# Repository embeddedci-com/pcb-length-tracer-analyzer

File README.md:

# pcb-trace-length-analyzer

A PCB trace length analyzer for KiCad boards. Reads a `.kicad_pcb`, finds the
interfaces on it -- DDR, Ethernet, USB, PCIe, MIPI, SD and any differential
pair -- measures how far each net is from the length it should be, and says what
to do about each one: match it where it is, open some room beside it, or route
it to a given length instead.

It can also fold the meanders in for you. That half is opt-in and experimental;
the analysis is the product.

DDR is the one it plans and tunes in full, because it is the hardest case: byte
lanes matched to their own strobe, address and command matched to the clock per
leg of the fly-by chain. The rest are recognised from the net names, measured,
and reported for you to confirm or correct.

It does not route. Nothing here creates a connection, moves a via, changes a
layer or rips anything up: a straight stretch of an existing track is replaced
by a longer path between the same two points, and everything else is left
exactly as it was.

**Reading a board is the solid half; writing to one is experimental.** The
report, the measurements and the triage are what this tool is for and are
checked against KiCad and against golden lengths. The changes it writes are
checked against KiCad's own DRC on the boards here and behave -- but no board
tuned by this has come back from a fab and been measured. Run DRC on the
result, look at the copper, and treat what comes out as a draft. Your own file
is never written to; the result is always a new one.

## Layout

```
cmd/pcb-trace-length-analyzer/        the command line tool
cmd/pcb-trace-length-analyzer-server/ the control plane on its own, for development
sexpr/                     KiCad S-expression parser, byte-exact round trip
geom/                      planar geometry: points, segments, three-point arcs, shapes
board/                     the board model: stackup, footprints, pads, tracks, zones
netlen/                    connectivity and length: what is routed, and how long it is
ddr/                       what a DDR interface is, and what has to match what
drc/                       clearance checking, indexed for speed
tune/                      meander generation and insertion
report/                    what the user reads before anything is changed
server/                    the HTTP control plane, mounted into a host application
webapp/                    React front end; src/ is a drop-in folder for the host
scripts/                   fixtures and verification, both driven by kicad-cli
demo-pcb/                  a real six-layer STM32MP257 + DDR4 board, used by the tests
testdata/                  net lengths extracted from KiCad, used as ground truth
```

## Using it

```
make report                       # analyse the demo board, change nothing
make tune                         # tune a copy into out/, then verify with KiCad
make serve                        # the web front end and the API on localhost:8091
make test                         # unit tests, no KiCad needed
make test-all                     # plus the end-to-end run against kicad-cli
```

Against your own board:

```
pcb-trace-length-analyzer board.kicad_pcb                                  # report only
pcb-trace-length-analyzer -apply -out tuned.kicad_pcb board.kicad_pcb      # report, ask, write
pcb-trace-length-analyzer -apply -only-group "byte lane 3" board.kicad_pcb # one group
pcb-trace-length-analyzer -clock-offset 2.5 board.kicad_pcb                # address 2.5% over clock
pcb-trace-length-analyzer -apply -expand board.kicad_pcb                   # spread tight buses first
pcb-trace-length-analyzer -open-clearance 0.25 board.kicad_pcb             # 0.25 mm between traces in the open
```

Reading a board never writes to it. `-apply` prints the same report first and
asks before it changes anything; `-yes` skips the prompt for scripts, and
`-dry-run` tunes in memory and reports without writing.

## What else is on the board

DDR is the hardest interface to length-match, not the only one. The board is
read for everything it carries — Ethernet, USB, PCIe, MIPI, SD/eMMC, and any
differential pair that belongs to none of them — and each one is listed with
what is wrong with it, so the choice of what to work on is yours:

```
Interfaces on this board: 10
  * DDR memory                ddr    71 nets, 71 routed  4 pair(s) out of intra-pair tolerance
    Ethernet RGMII (ETH1)     rgmii  17 nets,  2 routed  it has copper, but no net is joined end to end yet
    MIPI D-PHY (CSI)          mipi   12 nets,  0 routed  none of it is routed yet
    PCI Express               pcie   10 nets,  6 routed  it has copper, but no net is joined end to end yet
```

Recognition is by net name, which is a reading and not a proof: nothing in the
geometry says a pair is PCIe rather than SATA. So the tool proposes and you
decide. Each interface says what it matched on, and each can be reassigned to
whatever it really is — the picker lists what every family usually carries
("a MIPI link usually carries D0+/-, D1+/-, D2+/-, D3+/- and CK+/- either way"),
because that is how you recognise your own nets in a list. Reassigning applies
that family's limits and impedance targets, and says whether it could find that
family's structure in your names or only its pairs.

Two numbers decide an interface's impedance: how wide its tracks are, and how
far apart the two halves of a pair run. Where it is routed, both come off the
board and are offered for confirmation; where it is not, the tool asks. Either
way it says what the geometry comes out at against what the family usually wants
— 94.8 Ω differential against USB's 90, say — as an estimate from the stackup in
the board file. That is good for catching a width nowhere near its target and is
not a substitute for the fabricator's stackup and a field solver, which the
report says rather than implying otherwise.

Two questions get asked of each. Whether the two halves of every differential
pair match each other — which applies to nearly every fast interface, needs no
knowledge of the protocol, and is where this earns its keep on USB, PCIe and
MIPI. And whether the members of a source-synchronous group match the clock they
travel with — RGMII data against GTX_CLK, SD data against SDMMC_CK, MIPI lanes
against the clock lane. The default limits are widely published starting points
and are marked as such; the figure that matters is in your controller's layout
guide.

## What it understands about DDR

A length is only meaningful next to the right reference, so the nets are
classified before they are measured:

The first thing it reports is the fly-by chain, above anything about lengths,
because it decides whether those lengths mean anything. Address, command,
control and clock have to reach the devices in series and end in a termination
resistor: that topology is what makes write levelling work, and a T or a star
leaves a stub on every one of those nets. The report names the chain, says which
hops the board actually has, and says how it worked the order out — the order
decides which span each length is compared over, so it comes from the placement
and, where the copper joining the devices exists, from that.

On the demo board the answer is blunt: `U3 -> U4` is routed on all 26 nets,
`U4 -> U5` on none of them. KiCad reports no unconnected item for any of them,
because each is a net with copper on it.

- a **DQ** bit or a **DM** mask is matched to the **strobe of its own byte
  lane**, and to nothing else;
- the two halves of a **DQS** or **CK** pair are matched to each other, far more
  tightly;
- **address and command** lines are matched to the **clock**, optionally offset
  by a percentage of it.

Byte lanes are worked out from the topology, not from names. On a x32 interface
built from two x16 devices, `DQS2` serves the lane carrying `DQ16..DQ23`;
nothing in the name says so, and the classifier reads it off which device each
net lands on. Names that merely look differential — `CASN`, `ACTN`, `RESETN` —
stay single-ended.

**Fly-by nets are matched per leg.** Address and command lines reach the memory
devices in series, and equal total length with unequal legs still fails write
levelling, so each leg is its own group.

Lengths are reported both as millimetres, which is what you check in pcbnew, and
as picoseconds, computed per layer from the stackup. A net that changes layers
mid-run — which every fly-by net on the demo board does — is mismatched by about
30 per cent of the difference if it is matched geometrically, because a
microstrip millimetre and a stripline millimetre are not the same delay.

## Where a meander can go, and how much it can add

The room beside a track varies along it. Asking for one amplitude that holds over
a whole track finds nothing at all on a bus routed at its minimum clearance, so
the room is profiled in steps and the best non-overlapping stretches are used.

`Headroom` reports how much length that room could hold, per net, and the report
divides the shortfalls into the three things you can do about them:

| | |
|---|---|
| **have the room** | apply it |
| **short of room** | the tool adds what fits; opening space in the layout closes the rest |
| **need rerouting** | asking for more than a quarter of their own length, which no meander supplies |

It also measures the clear space beside the buses these nets run in, which bounds
what re-spacing a bus could add — the number to look at before deciding that
moving the neighbours is worth it.

## Spreading a bus into space it has beside it

A bus routed at its minimum clearance has nowhere to fold a meander, however
much clear space lies beside the bus as a whole. `-expand` opts into moving it:
each trace steps sideways at 45 degrees inside its own extent, runs along its
new line, and steps back, so gaps open between them. Endpoints do not move, the
traces keep their order, and nothing is rerouted — but traces the user did not
select do move, so it is off by default and the report names every one of them.

On the demo board it takes the total added from 58.8 mm to 61.1 mm and brings
one more net inside tolerance. Two properties of the board bound what it can
achieve, and the report says which
one it hit for every bus it could not help. Moving a trace lengthens it, so a
trace that needs no length cannot move; and the gap a trace gets is how much
further the trace beyond it moved, so the outermost trace's own requirement caps
everything inside it. Byte lane 2 is the instructive case: 5 mm of clear space,
all of it behind DQ19, the one trace on the lane already at the target.

## Clearance in the open, not around the BGA

A fine-pitch BGA is the hardest part of a board to route, so the clearance on
the netlist is usually whatever got the escape out — 0.1 mm is common — and the
whole board inherits it. Between the components there is normally more room.

`-open-clearance` (0.2 mm by default, 0 to switch it off) holds this tool to a
wider figure away from the components while leaving the board's own rules in
force around them; `-open-margin` sets how far outside a component's pads still
counts as being around it. A differential pair is exempt either way. It only
tightens — a board whose own rule is stricter keeps it — and it applies to every
measurement, not just the copper written out, so the room the report promises is
the room the tuner works to.

## Meandering can only add length

There is no way to shorten a track without rerouting it. So a group's target
starts at what its reference asks for and is then raised to clear the group's
longest member; where that happens the report says so, and says by how much the
reference itself now falls short.

Where the target cannot be reached at all, the tool adds what fits and reports
the rest. It does not quietly stop, and it does not pretend.

## What it will not do

It will not make anything worse. A meander is drawn only if the copper it adds
clears every design rule, and only if the complete replacement — the meander and
the untouched ends of the original track alike — is no closer to anything than
the track it replaces. That distinction matters on a real board: the demo board
already has 687 violations, and re-creating an unchanged stretch of track
inherits whatever it was already too close to.

It will not exceed its brief either. Meanders keep three track widths of clear
space between their legs, because coupling between them eats the delay the
meander was added for; where a differential pair's halves are too far apart to
fix by padding one of them, that is reported as needing a reroute rather than
done badly.

## Seeing it

A length in a table is a claim. `/api/pcb-trace-length-analyzer/sessions/{id}/preview/board.json`
and its `geometry.bin` are the copper that claim was written into: the board as
triangles a browser can draw, in the format the EMI Analyzer's viewer already
reads, so the front end reuses that viewer rather than growing a second one.
`?of=result` is the board after tuning, and flipping between the two at the same
zoom is the only way to see a meander — it is obvious on screen and invisible in
a diff.

The front end picks a net to highlight and frames it, marks the nets an apply
changed, and keeps the view when you flip between before and after. Copper pours
are off by default: they are most of a board's copper by area, they sit under
the traces this tool changes, and drawing them doubles the download.

## The board's own design rules

A `.kicad_dru` is read as far as it can be trusted. What matters is the one kind
of rule that changes where copper may go: a clearance with a condition. The demo
board has five, and three say the same important thing — inside a BGA's
courtyard, 0.1 mm is allowed rather than the 0.2 mm the net class asks for.

Those used to be reported as "not interpreted" and the tool worked to the
stricter figure. That is the right default and it cost nothing while the tool
only lengthened existing traces — being stricter means declining to put a
meander somewhere it would have fitted. It stopped being free once the tool
could create copper: **a BGA ball cannot be escaped at 0.2 mm**, so every one of
the demo board's 26 second-hop connections was refused as having no way through.

Reading a rule that *relaxes* a clearance is a different risk from ignoring one,
so three things hold it down. Only conditions it fully understands are used, and
anything else is named in the report rather than guessed at. A relaxation
applies only when the condition holds for **both** pieces of copper, where KiCad
asks about one. And "inside a courtyard" means wholly inside, where KiCad says
intersects. All three are stricter than KiCad, in the direction that declines
rather than allows — and the flow still ends by asking KiCad, which is the only
authority on its own rule language.

## Where copper may go

Deciding how much length a net needs is arithmetic. Deciding **where** to put it
is a judgement about the board, and "wherever there is room" is not the same
answer as "wherever you would want it" — room beside a trace can be in a BGA
fanout, under a connector, across a split in a reference plane, or in the one
part of the board somebody has left clear on purpose. A clearance check cannot
tell the difference.

So the person who drew the board says. In the web front end, the step before
applying is a board view with a **Draw an area** button: drag out the regions
the tool may meander into, and they are listed and can be removed. On the
command line, `-area x0,y0,x1,y1` in board millimetres, repeated for several.

**Suggest areas** fills them in first, so you adjust rather than invent. A blank
board and "draw where copper may go" is a worse question than it looks — the
answer depends on where the nets that need length run and where there happens to
be space beside them, both of which the tool has already measured and you would
have to hunt for. On the demo board it proposes two regions holding 74.0 mm of
the 75.9 mm the whole board offers. They are not a recommendation: the tool
cannot see a connector, a plane split, or the part of the board you were keeping
clear. They are where the length could come from.

Each area carries **its own minimum spacing**, because that is where you know
it. A global "keep 0.25 mm apart away from the components" makes the tool guess
what "away from the components" means; "keep 0.25 mm apart in here" needs
nothing guessed, since you drew the here. It only ever tightens — an area is
somewhere you chose to put copper, not a licence to crowd it.

Leaving it empty means anywhere, which is what the tool did before and is right
for a first look. Once areas are given, nothing is added outside them — not a
meander, not a bus being spread — and the room reported drops to what is
actually usable, so the plan you read is the plan you get.

The area is a statement about where copper may be, not about where centrelines
may be: a meander wanders sideways from the track it is folded into, so the
room at each point is capped by the distance to the area's edge as surely as by
a neighbouring track.

**And it tells you whether the area will do.** Drawing a region and being told
nothing is only half a tool, so the room inside it is measured — about a second,
and faster with an area than without, since there is less to look at — and
reported as a verdict: how much of what is needed is reachable, per group, and
what the shortfall is made of. That last part is the useful half:

> 43.554 mm of the 235.223 mm needed is reachable inside the areas: 1 of 36 nets
> have all the room they need. Of the 191.669 mm still missing, 40.474 mm is on
> nets that are merely short of room — a bigger area may reach it. 151.195 mm is
> on 20 nets asking for more than a quarter of their own length, which no area
> can supply: those need rerouting, not more space.

The two halves of a shortfall are different problems. One is answered by drawing
a bigger area; the other never is, because the limit is the track rather than
the space around it.

## Verifying the result

The tool's own checks are not the last word, and it does not interpret custom
`.kicad_dru` rules. Every run ends by telling you to ask KiCad, and
`make verify` does it:

```
scripts/verify-with-kicad.sh before.kicad_pcb after.kicad_pcb
```

That runs KiCad's DRC on both boards and compares them, and reads the net
lengths back out of KiCad to confirm they grew by what was claimed. There is no
kicad-cli command that prints a net length, so `scripts/golden-lengths.sh` gets
them out with a design rule that every net violates, which makes the DRC engine
state the length it measured. The same trick produced
`testdata/golden-lengths.json`, against which the length engine is tested.

## The web front end

`make serve` builds `webapp/` and serves it alongside the API at
<http://localhost:8091/tools/pcb-trace-length-analyzer>. Upload a board, read the report, set the
tolerances and the clock offset, choose what to change, and download the result — the same
report-then-confirm-then-apply order the command line uses, for the same reason.

Upload the `.kicad_pro` along with the board. Without it there are no net classes, so every
clearance falls back to the board minimum and the tool works to rules the design did not
set. The report says when it is missing.

### How it will ship

The same way the EMI analyzer does: mounted into embeddedci-server rather than deployed
beside it. There is no container, no queue and no worker, because the engine is Go and runs
in process — reading a 2.4 MB board and measuring its whole DDR interface takes about
150 ms, so a request answers directly.

| half | linked by | seam |
|---|---|---|
| `server/` | one `replace` in `embeddedci-server/go.mod` → `../pcb-trace-length-analyzer` | `server.New(deps).Mount(mux, prefix, userAuth)` |
| `webapp/src/` | a Vite alias → `embeddedci-server/webapp/src/pcb-trace-length-analyzer/` | `autorouteRoutes(api)`, a route fragment with no prefix of its own |

One module and one `replace`, deliberately: a path-based link per half is what made CI need
two checkouts last time.

Everything the host has to supply is an interface in [server/deps.go](server/deps.go):
where to keep an uploaded board (`Store`), and who is asking. This package authenticates
nobody — it refuses to act for an identity the host did not vouch for with `WithUser`, and
an anonymous request is refused rather than filed under nobody.

`cmd/pcb-trace-length-analyzer-server` is a development harness, not a deployment target. It has no
authentication and runs every request as whatever `-user` says.

## The demo board

`demo-pcb/` is a real work-in-progress six-layer board: an STM32MP257 with two
x16 DDR4 devices in a fly-by chain. It is the fixture for almost every test
here, and it is genuinely unfinished in ways worth knowing about, because the
tests assert them:

- the 44 point-to-point nets — the DQ bits, strobes and masks — are fully routed;
- **not one of the 27 fly-by nets has its second leg routed**, from the near
  device to the far one, and only the clock pair has any copper at its
  termination. KiCad's DRC reports no unconnected item for any DDR net and sums
  length straight across the gap, so this tool works routing completeness out
  from the geometry instead;
- byte lanes 0, 1 and 2 were tuned by hand and sit within about 0.7 mm; lane 3
  was never touched and is spread over 7.6 mm;
- **the byte lanes are routed at exactly the minimum DDR clearance.** The
  nearest neighbour of one DQ24 segment sits 0.2000 mm away against a 0.2 mm
  rule. The room beside a track is not uniform along it, though, and profiling
  it in steps finds sixty-seven times more usable capacity on byte lane 3 than
  asking for one amplitude over the whole track — enough to give DQ24 its full
  7.609 mm;
- **the fly-by bus is matched against a clock nearly twice the length of its
  shortest member.** A11 is asked to grow by 14.251 mm on a 16.888 mm route. No
  meander does that, so the tool says so rather than trying: twenty of the
  thirty-six candidates are flagged as needing a reroute, which is why the
  shortfall stays large however good the tuning gets.

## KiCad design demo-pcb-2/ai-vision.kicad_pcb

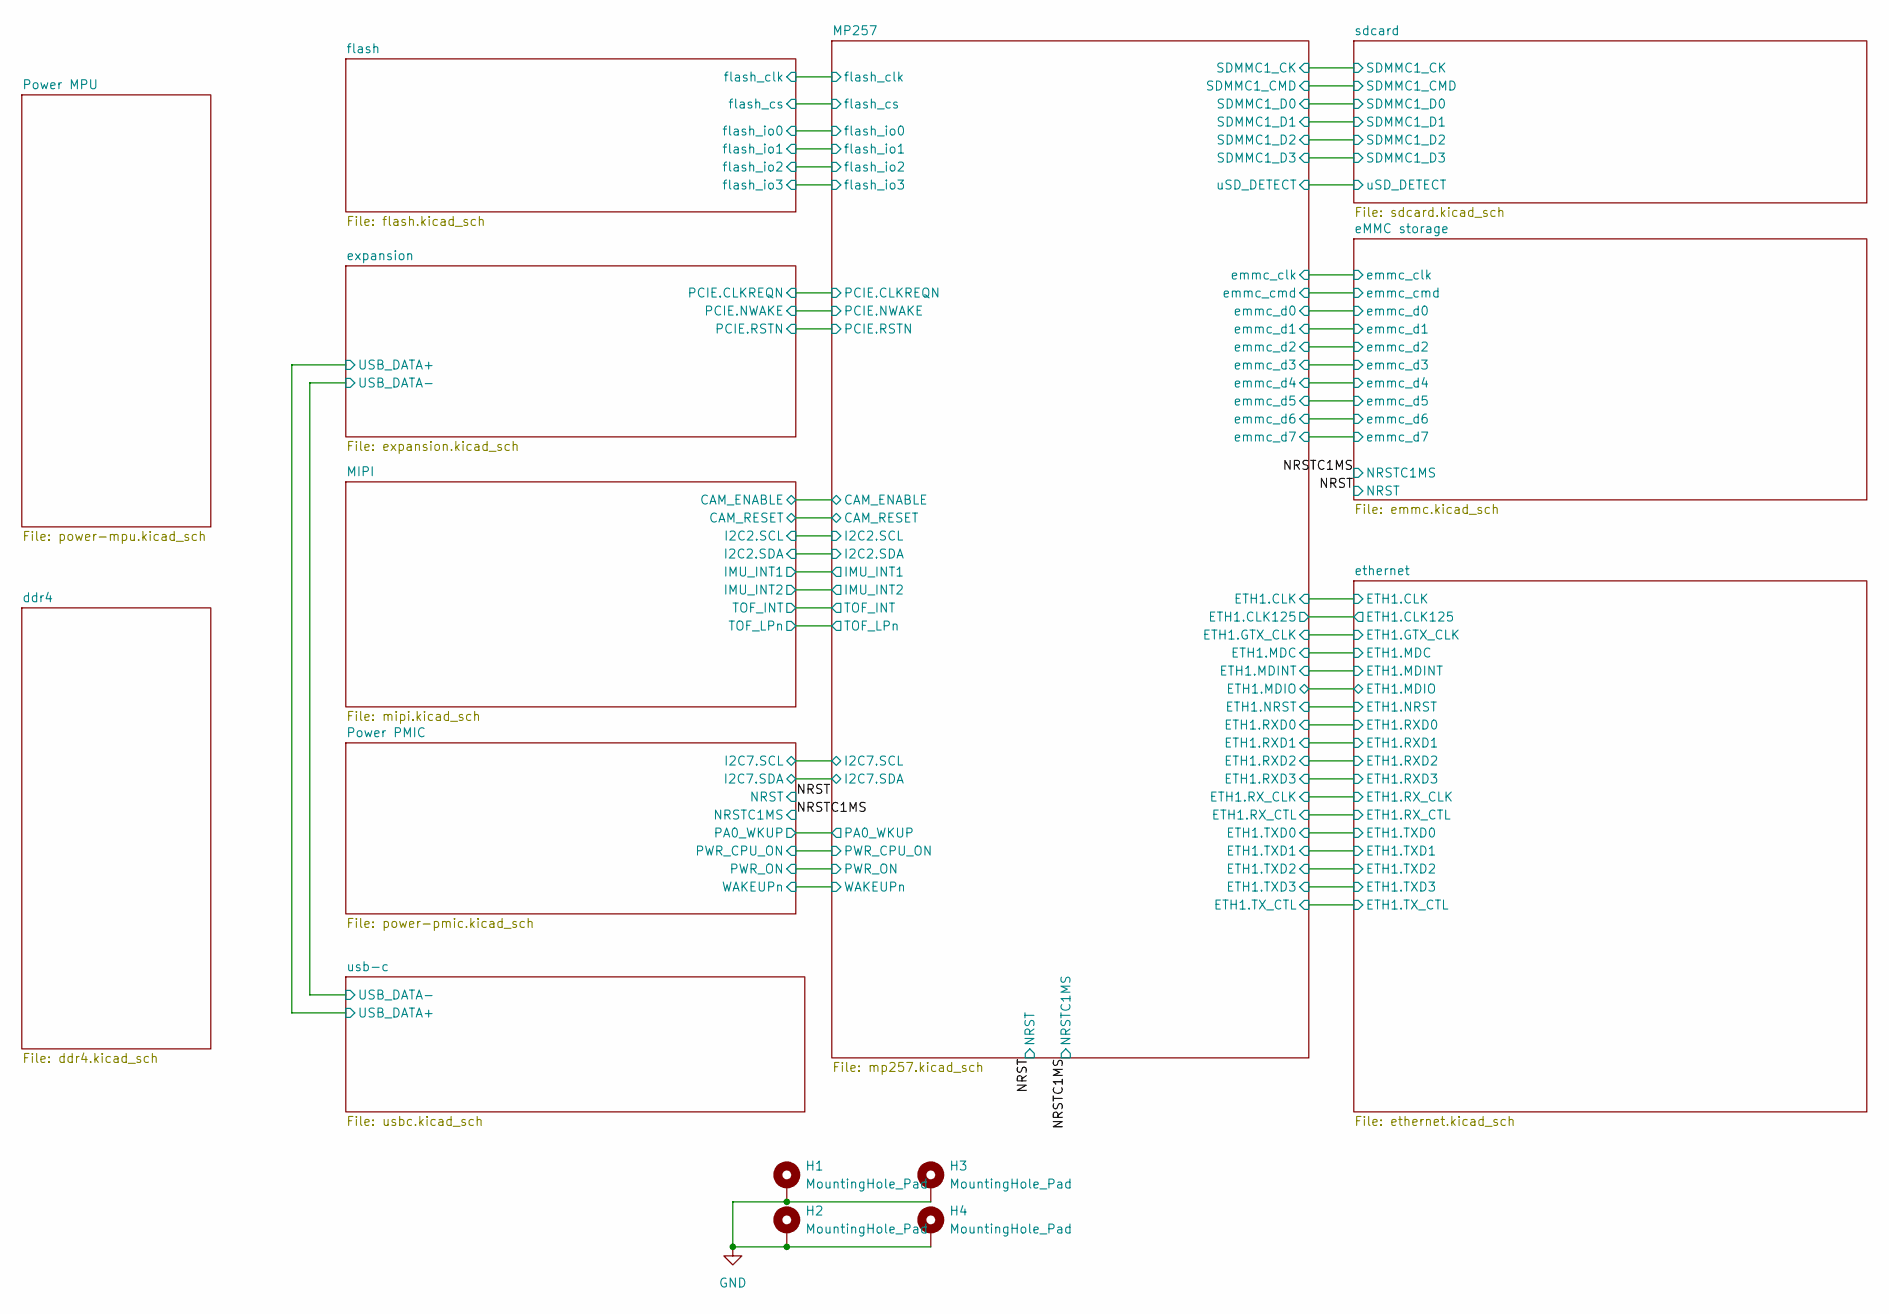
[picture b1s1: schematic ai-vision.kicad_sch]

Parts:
H1, H2, H3, H4: MountingHole_Pad; MountingHole_2.2mm_M2_Pad_Via

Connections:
GND: H1.1 (1_1), H2.1 (1_1), H3.1 (1_1), H4.1 (1_1); also elsewhere on the board

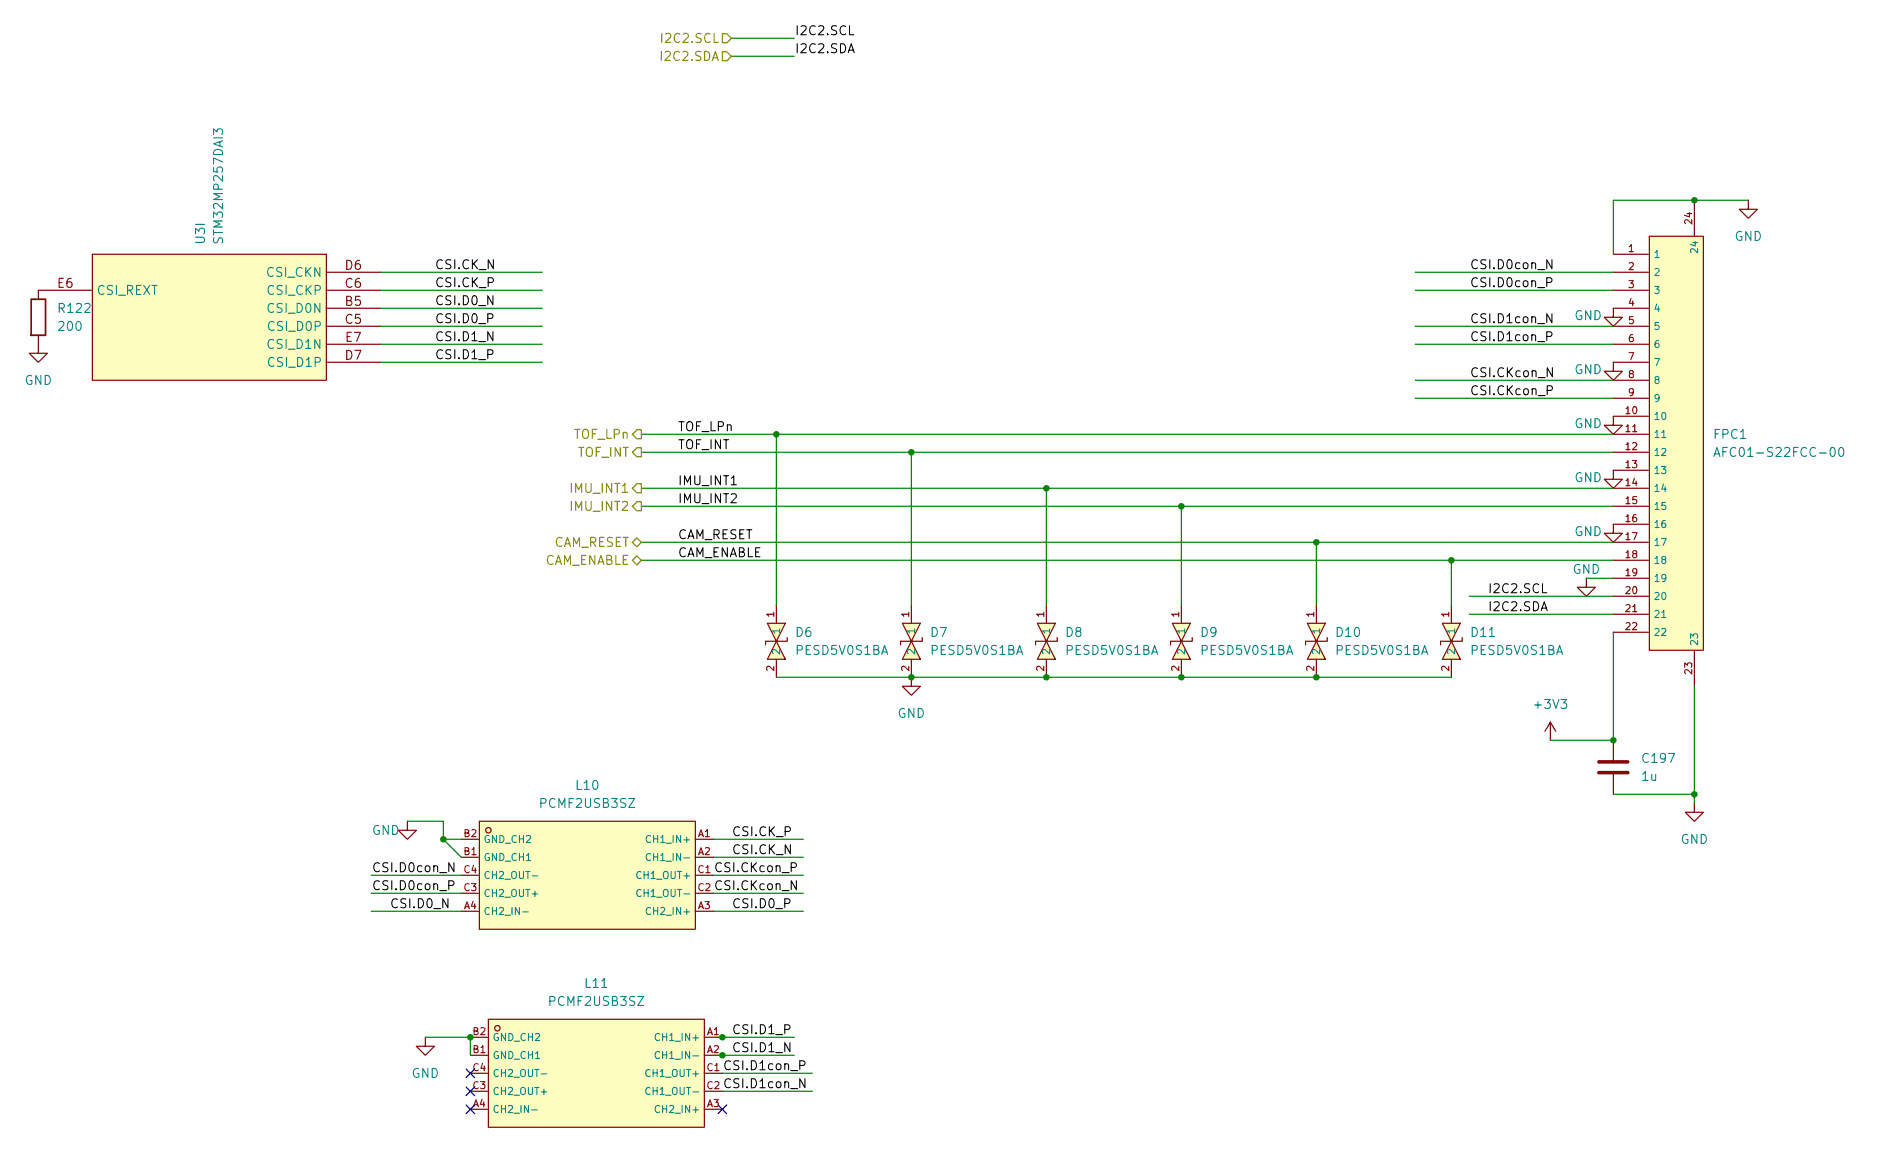
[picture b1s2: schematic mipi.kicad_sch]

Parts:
C197: 1u; C_0402_1005Metric; LCSC C52923
D6, D7, D8, D9, D10, D11: PESD5V0S1BA; C2827694_SOD-323_L1_7-W1_3-LS2_5-BI; LCSC C2827694
FPC1: AFC01-S22FCC-00; C262275_FPC-SMD_AFC01-S22FCC-00; LCSC C262275
L10, L11: PCMF2USB3SZ; C5259148_WLCSP-10_L1_6-W1_2-P0_40-BL_PCMF2USB3SZ; LCSC C5259148
R122: 200; R_0402_1005Metric; LCSC C25087
U3: STM32MP257DAI3; C39969643_TFBGA-436_L18_0-W18_0-0_80-TL_STM32MP257FAI3; PART_TYPE IC; LCSC C39969643

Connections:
+3V3: C197.1, FPC1.22; also elsewhere on the board
/MIPI/CAM_ENABLE: D11.1, FPC1.18; also elsewhere on the board
/MIPI/CAM_RESET: D10.1, FPC1.17; also elsewhere on the board
/MIPI/CSI.CK_N: L10.A2 (CH1_IN-), U3.D6 (CSI_CKN)
/MIPI/CSI.CK_P: L10.A1 (CH1_IN+), U3.C6 (CSI_CKP)
/MIPI/CSI.CKcon_N: FPC1.8, L10.C2 (CH1_OUT-)
/MIPI/CSI.CKcon_P: FPC1.9, L10.C1 (CH1_OUT+)
/MIPI/CSI.D0_N: L10.A4 (CH2_IN-), U3.B5 (CSI_D0N)
/MIPI/CSI.D0_P: L10.A3 (CH2_IN+), U3.C5 (CSI_D0P)
/MIPI/CSI.D0con_N: FPC1.2, L10.C4 (CH2_OUT-)
/MIPI/CSI.D0con_P: FPC1.3, L10.C3 (CH2_OUT+)
/MIPI/CSI.D1_N: L11.A2 (CH1_IN-), U3.E7 (CSI_D1N)
/MIPI/CSI.D1_P: L11.A1 (CH1_IN+), U3.D7 (CSI_D1P)
/MIPI/CSI.D1con_N: FPC1.5, L11.C2 (CH1_OUT-)
/MIPI/CSI.D1con_P: FPC1.6, L11.C1 (CH1_OUT+)
/MIPI/I2C2.SCL: FPC1.20; also elsewhere on the board
/MIPI/I2C2.SDA: FPC1.21; also elsewhere on the board
/MIPI/IMU_INT1: D8.1, FPC1.14; also elsewhere on the board
/MIPI/IMU_INT2: D9.1, FPC1.15; also elsewhere on the board
/MIPI/TOF_INT: D7.1, FPC1.12; also elsewhere on the board
/MIPI/TOF_LPn: D6.1, FPC1.11; also elsewhere on the board
GND: C197.2, D6.2, D7.2, D8.2, D9.2, D10.2, D11.2, FPC1.1, FPC1.4, FPC1.7, FPC1.10, FPC1.13, FPC1.16, FPC1.19, FPC1.23, FPC1.24, L10.B1 (GND_CH1), L10.B2 (GND_CH2), L11.B1 (GND_CH1), L11.B2 (GND_CH2), R122.2; also elsewhere on the board
unnamed: R122.1, U3.E6 (CSI_REXT)

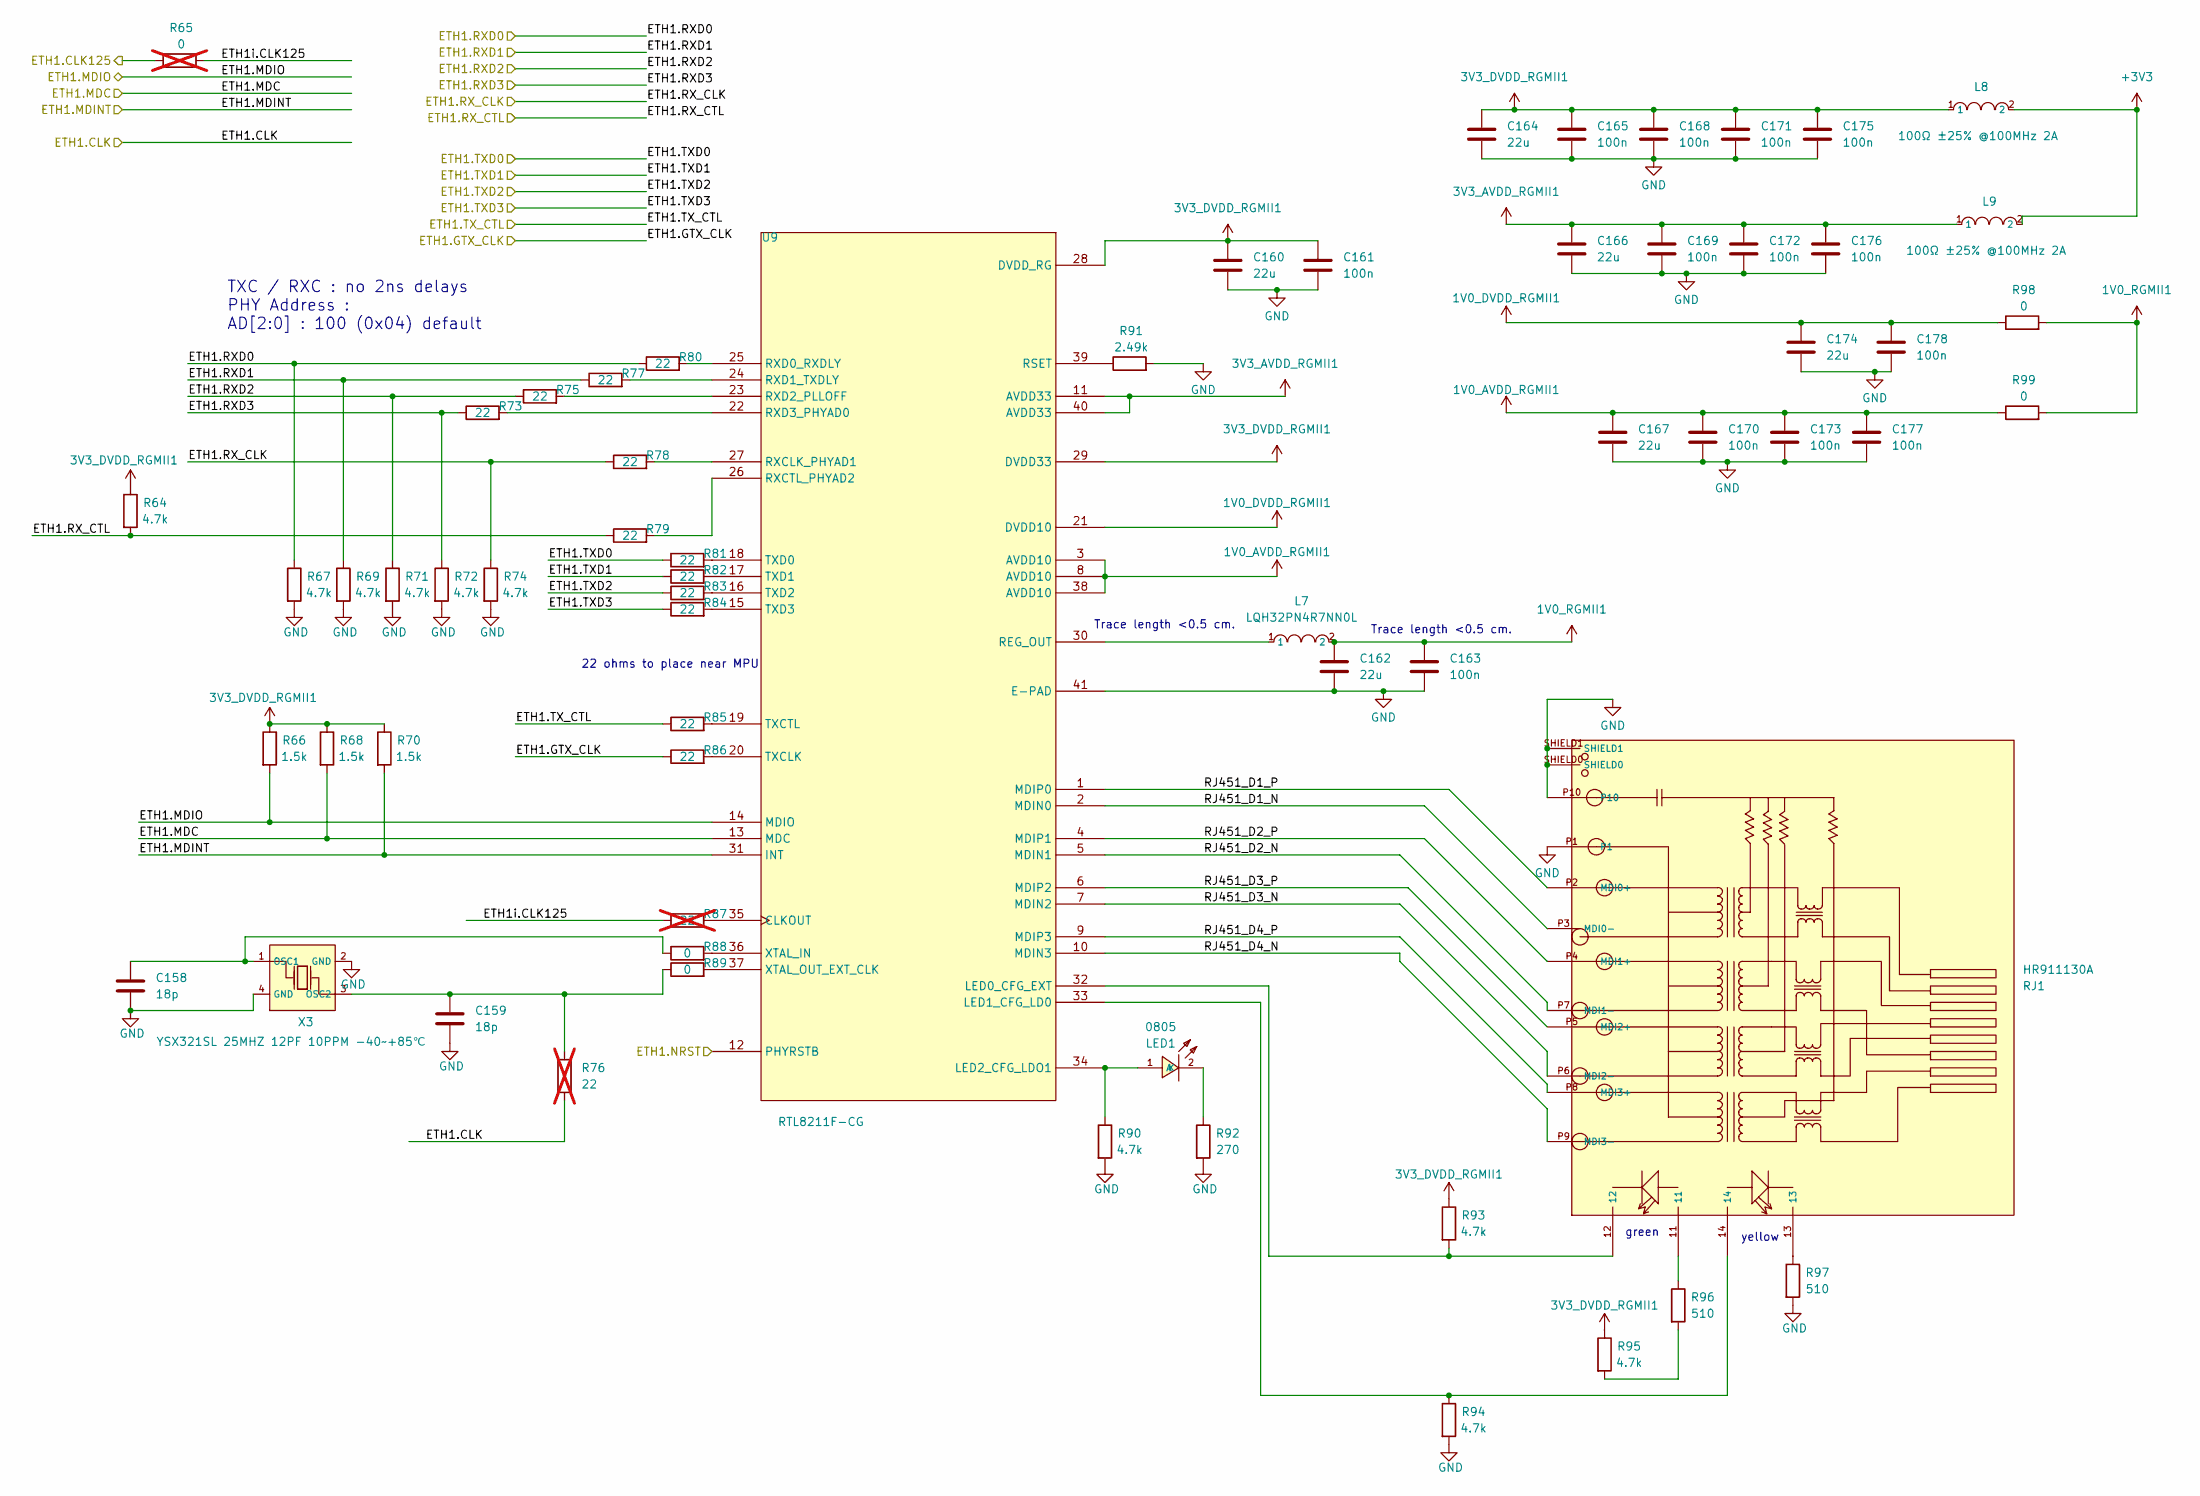
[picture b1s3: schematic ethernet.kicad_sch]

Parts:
C158, C159: 18p; C_0402_1005Metric; LCSC C1549
C160, C162, C164, C166, C167, C174: 22u; C_0805_2012Metric; LCSC C45783
C161, C163, C165, C168, C169, C170, C171, C172, C173, C175, C176, C177, C178: 100n; C_0402_1005Metric; LCSC C307331
L7: LQH32PN4R7NN0L; C98021_IND-SMD_L3_2-W2_5_82103C; LCSC C98021
L8, L9: 100Ω ±25% @100MHz 2A; C76893_L0603; LCSC C76893
LED1: 0805; C2297_LED0805-R-RD; LCSC C2297
R64, R67, R69, R71, R72, R74, R90, R93, R94, R95: 4.7k; R_0402_1005Metric; LCSC C25900
R65: 0; R_0402_1005Metric; LCSC C17168; not fitted
R66, R68, R70: 1.5k; R_0402_1005Metric; LCSC C25867
R73, R75, R77, R78, R79, R80, R81, R82, R83, R84, R85, R86: 22; R_0402_1005Metric; LCSC C25092
R76, R87: 22; R_0402_1005Metric; LCSC C25092; not fitted
R88, R89, R98, R99: 0; R_0402_1005Metric; LCSC C17168
R91: 2.49k; R_0402_1005Metric; LCSC C2933083
R92: 270; R_0603_1608Metric; LCSC C22966
R96, R97: 510; R_0402_1005Metric; LCSC C25123
RJ1: HR911130A; C54408_RJ45-TH_HR911130A; LCSC C54408
U9: RTL8211F-CG; C187932_WQFN-40_L5_0-W5_0-P0_4-BL-EP; MANUFACTURER_PART_NUMBER RTL8211F-CG; LCSC C187932
X3: YSX321SL 25MHZ 12PF 10PPM -40~+85℃; C9006_CRYSTAL-SMD_4P-L3_2-W2_5-BL; LCSC C9006

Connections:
1V0_AVDD_RGMII1: C167.1, C170.1, C173.1, C177.1, R99.1, U9.3 (AVDD10), U9.8 (AVDD10), U9.38 (AVDD10)
1V0_DVDD_RGMII1: C174.1, C178.1, R98.1, U9.21 (DVDD10)
1V0_RGMII1: C162.1, C163.1, L7.2, R98.2, R99.2
3V3_AVDD_RGMII1: C166.1, C169.1, C172.1, C176.1, L9.1, U9.11 (AVDD33), U9.40 (AVDD33)
3V3_DVDD_RGMII1: C160.1, C161.1, C164.1, C165.1, C168.1, C171.1, C175.1, L8.1, R64.1, R66.1, R68.1, R70.1, R93.1, R95.1, U9.28 (DVDD_RG), U9.29 (DVDD33)
+3V3: L8.2, L9.2; also elsewhere on the board
/MP257/ETH1.CLK125: R65.1; also elsewhere on the board
/MP257/ETH1.NRST: U9.12 (PHYRSTB); also elsewhere on the board
/ethernet/ETH1.CLK: R76.2; also elsewhere on the board
/ethernet/ETH1.GTX_CLK: R86.1; also elsewhere on the board
/ethernet/ETH1.MDC: R68.2, U9.13 (MDC); also elsewhere on the board
/ethernet/ETH1.MDINT: R70.2, U9.31 (INT); also elsewhere on the board
/ethernet/ETH1.MDIO: R66.2, U9.14 (MDIO); also elsewhere on the board
/ethernet/ETH1.RXD0: R67.1, R80.1; also elsewhere on the board
/ethernet/ETH1.RXD1: R69.1, R77.1; also elsewhere on the board
/ethernet/ETH1.RXD2: R71.1, R75.1; also elsewhere on the board
/ethernet/ETH1.RXD3: R72.1, R73.1; also elsewhere on the board
/ethernet/ETH1.RX_CLK: R74.1, R78.1; also elsewhere on the board
/ethernet/ETH1.RX_CTL: R64.2, R79.1; also elsewhere on the board
/ethernet/ETH1.TXD0: R81.1; also elsewhere on the board
/ethernet/ETH1.TXD1: R82.1; also elsewhere on the board
/ethernet/ETH1.TXD2: R83.1; also elsewhere on the board
/ethernet/ETH1.TXD3: R84.1; also elsewhere on the board
/ethernet/ETH1.TX_CTL: R85.1; also elsewhere on the board
/ethernet/ETH1i.CLK125: R65.2, R87.1
/ethernet/RJ451_D1_N: RJ1.P3 (MDI0-), U9.2 (MDIN0)
/ethernet/RJ451_D1_P: RJ1.P2 (MDI0+), U9.1 (MDIP0)
/ethernet/RJ451_D2_N: RJ1.P7 (MDI1-), U9.5 (MDIN1)
/ethernet/RJ451_D2_P: RJ1.P4 (MDI1+), U9.4 (MDIP1)
/ethernet/RJ451_D3_N: RJ1.P6 (MDI2-), U9.7 (MDIN2)
/ethernet/RJ451_D3_P: RJ1.P5 (MDI2+), U9.6 (MDIP2)
/ethernet/RJ451_D4_N: RJ1.P9 (MDI3-), U9.10 (MDIN3)
/ethernet/RJ451_D4_P: RJ1.P8 (MDI3+), U9.9 (MDIP3)
GND: C158.2, C159.2, C160.2, C161.2, C162.2, C163.2, C164.2, C165.2, C166.2, C167.2, C168.2, C169.2, C170.2, C171.2, C172.2, C173.2, C174.2, C175.2, C176.2, C177.2, C178.2, R67.2, R69.2, R71.2, R72.2, R74.2, R90.2, R91.2, R92.2, R94.2, R97.2, RJ1.P1, RJ1.P10, RJ1.SHIELD0, RJ1.SHIELD1, U9.41 (E-PAD), X3.2 (GND), X3.4 (GND); also elsewhere on the board
unnamed: LED1.1 (A), R90.1, U9.34 (LED2_CFG_LDO1)
unnamed: LED1.2 (K), R92.1
unnamed: R95.2, R96.2
unnamed: R96.1, RJ1.11
unnamed: R97.1, RJ1.13
unnamed: R87.2, U9.35 (CLKOUT)
unnamed: R93.2, RJ1.12, U9.32 (LED0_CFG_EXT)
unnamed: R94.1, RJ1.14, U9.33 (LED1_CFG_LD0)
unnamed: L7.1, U9.30 (REG_OUT)
unnamed: R91.1, U9.39 (RSET)
unnamed: R78.2, U9.27 (RXCLK_PHYAD1)
unnamed: R79.2, U9.26 (RXCTL_PHYAD2)
unnamed: R80.2, U9.25 (RXD0_RXDLY)
unnamed: R77.2, U9.24 (RXD1_TXDLY)
unnamed: R75.2, U9.23 (RXD2_PLLOFF)
unnamed: R73.2, U9.22 (RXD3_PHYAD0)
unnamed: R86.2, U9.20 (TXCLK)
unnamed: R85.2, U9.19 (TXCTL)
unnamed: R81.2, U9.18 (TXD0)
unnamed: R82.2, U9.17 (TXD1)
unnamed: R83.2, U9.16 (TXD2)
unnamed: R84.2, U9.15 (TXD3)
unnamed: R88.2, U9.36 (XTAL_IN)
unnamed: R89.2, U9.37 (XTAL_OUT_EXT_CLK)
unnamed: C158.1, R88.1, X3.1 (OSC1)
unnamed: C159.1, R76.1, R89.1, X3.3 (OSC2)

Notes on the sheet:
Trace length <0.5 cm.
22 ohms to place near MPU
green
yellow
TXC / RXC : no 2ns delays PHY Address : AD[2:0] : 100 (0x04) default

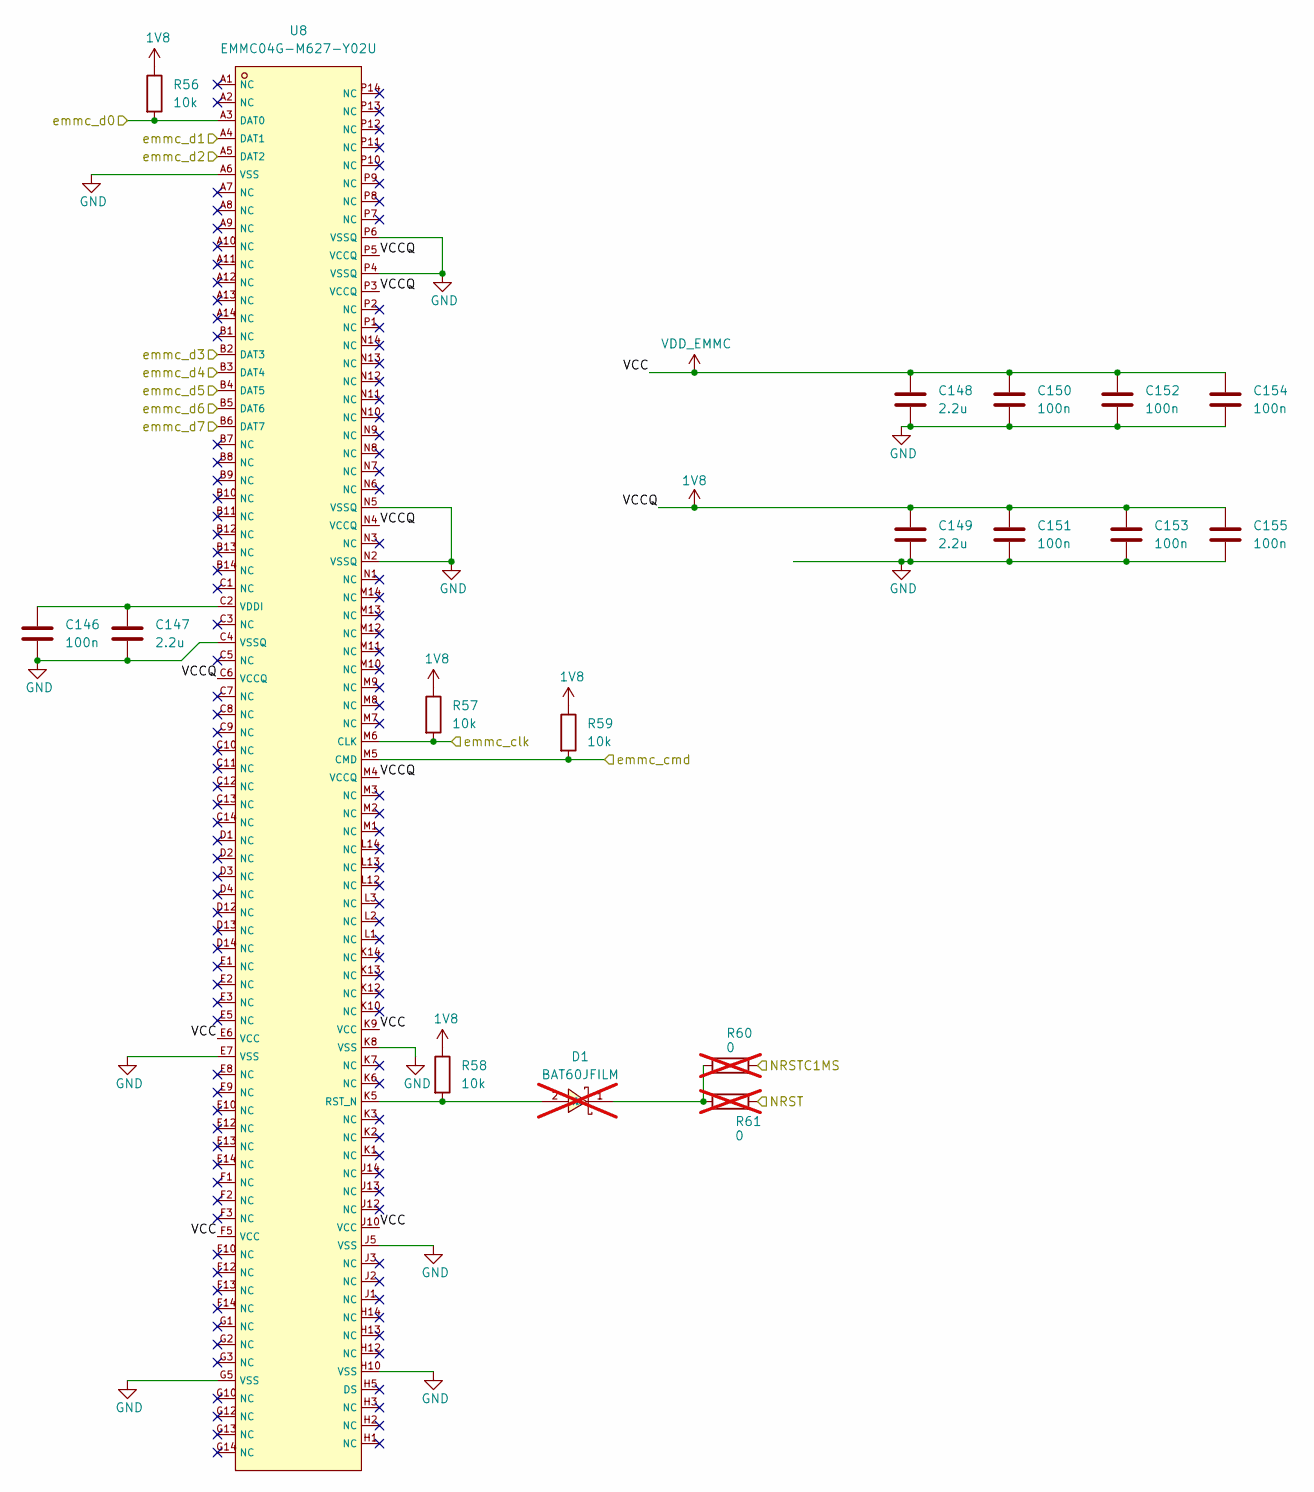
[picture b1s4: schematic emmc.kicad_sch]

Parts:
C146, C150, C151, C152, C153, C154, C155: 100n; C_0402_1005Metric; LCSC C307331
C147, C148, C149: 2.2u; C_0805_2012Metric; LCSC C377773
D1: BAT60JFILM; C133103_SOD-323_L1_8-W1_3-LS2_5-RD; LCSC C133103; not fitted
R56, R57, R58, R59: 10k; R_0402_1005Metric; LCSC C25744
R60, R61: 0; R_0402_1005Metric; LCSC C17168; not fitted
U8: EMMC04G-M627-Y02U; C43168982_FBGA-153_L13_0-W11_5-P0_50_MKEMA032GD1E-C; LCSC C43168982

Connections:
1V8: C149.1, C151.1, C153.1, C155.1, R56.1, R57.1, R58.1, R59.1, U8.C6 (VCCQ), U8.M4 (VCCQ), U8.N4 (VCCQ), U8.P3 (VCCQ), U8.P5 (VCCQ); also elsewhere on the board
/MP257/emmc_clk: R57.2, U8.M6 (CLK); also elsewhere on the board
/MP257/emmc_cmd: R59.2, U8.M5 (CMD); also elsewhere on the board
/MP257/emmc_d0: R56.2, U8.A3 (DAT0); also elsewhere on the board
/MP257/emmc_d1: U8.A4 (DAT1); also elsewhere on the board
/MP257/emmc_d2: U8.A5 (DAT2); also elsewhere on the board
/MP257/emmc_d3: U8.B2 (DAT3); also elsewhere on the board
/MP257/emmc_d4: U8.B3 (DAT4); also elsewhere on the board
/MP257/emmc_d5: U8.B4 (DAT5); also elsewhere on the board
/MP257/emmc_d6: U8.B5 (DAT6); also elsewhere on the board
/MP257/emmc_d7: U8.B6 (DAT7); also elsewhere on the board
/NRST: R61.2; also elsewhere on the board
/NRSTC1MS: R60.2; also elsewhere on the board
GND: C146.2, C147.2, C148.2, C149.2, C150.2, C151.2, C152.2, C153.2, C154.2, C155.2, U8.A6 (VSS), U8.C4 (VSSQ), U8.E7 (VSS), U8.G5 (VSS), U8.H10 (VSS), U8.J5 (VSS), U8.K8 (VSS), U8.N2 (VSSQ), U8.N5 (VSSQ), U8.P4 (VSSQ), U8.P6 (VSSQ); also elsewhere on the board
unnamed: D1.2 (A), R58.2, U8.K5 (RST_N)
unnamed: D1.1 (K), R60.1, R61.1
unnamed: C146.1, C147.1, U8.C2 (VDDI)
VDD_EMMC: C148.1, C150.1, C152.1, C154.1, U8.E6 (VCC), U8.F5 (VCC), U8.J10 (VCC), U8.K9 (VCC); also elsewhere on the board

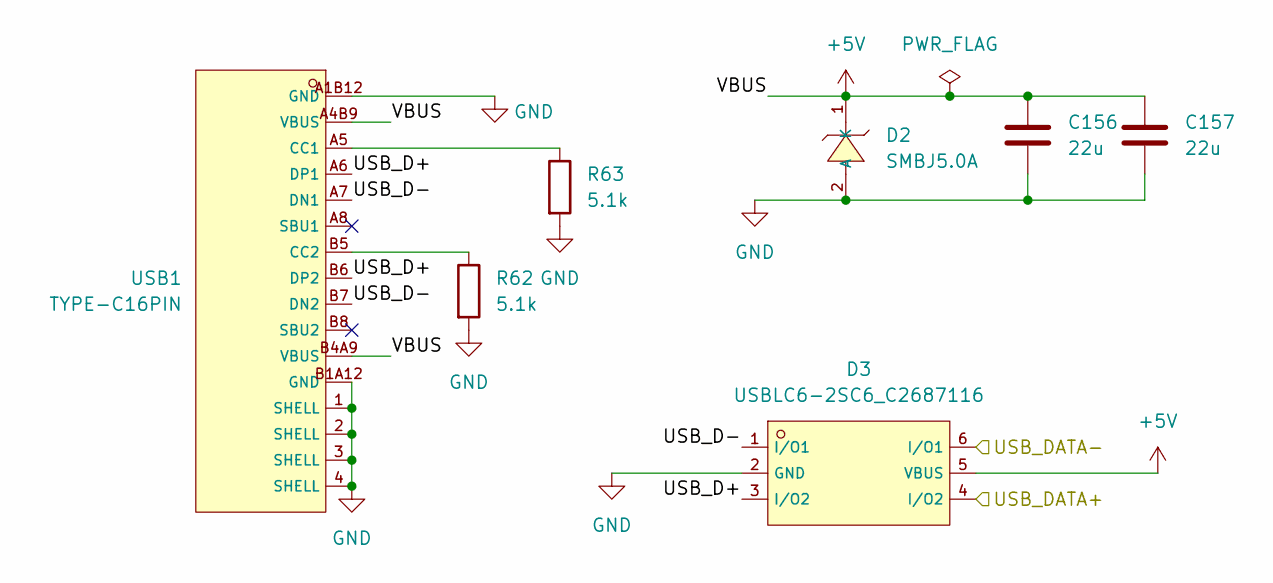
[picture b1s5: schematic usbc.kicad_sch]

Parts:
C156, C157: 22u; C_0805_2012Metric; LCSC C45783
D2: SMBJ5.0A; C19077558_SMB_L4_6-W3_6-LS5_4-RD; LCSC C19077558
D3: USBLC6-2SC6_C2687116; C2687116_SOT-23-6_L2_9-W1_6-P0_95-LS2_8-BL; LCSC C2687116
R62, R63: 5.1k; R_0402_1005Metric; LCSC C25905
USB1: TYPE-C16PIN; C393939_USB-C-SMD_TYPE-C16PIN; LCSC C393939

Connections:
+5V: C156.1, C157.1, D2.1 (K), D3.5 (VBUS), USB1.A4B9 (VBUS), USB1.B4A9 (VBUS); also elsewhere on the board
/expansion/USB_DATA+: D3.4 (I/O2); also elsewhere on the board
/expansion/USB_DATA-: D3.6 (I/O1); also elsewhere on the board
/usb-c/USB_D+: D3.3 (I/O2), USB1.A6 (DP1), USB1.B6 (DP2)
/usb-c/USB_D-: D3.1 (I/O1), USB1.A7 (DN1), USB1.B7 (DN2)
GND: C156.2, C157.2, D2.2 (A), D3.2 (GND), R62.2, R63.2, USB1.1 (SHELL), USB1.2 (SHELL), USB1.3 (SHELL), USB1.4 (SHELL), USB1.A1B12 (GND), USB1.B1A12 (GND); also elsewhere on the board
unnamed: R63.1, USB1.A5 (CC1)
unnamed: R62.1, USB1.B5 (CC2)
